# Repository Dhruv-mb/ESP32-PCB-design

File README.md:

ESP32-C3 Mini Evaluation Board

📌 Project Overview

This repository contains the KiCad hardware design files for a custom, compact ESP32-C3 (WROOM-02) mini evaluation board. Designed from scratch, this board functions as a standalone, breadboard-friendly tool tailored for rapid embedded development, IoT prototyping, and testing.

⚙️ Key Hardware Features

Microcontroller Core: Powered by the ESP32-C3-WROOM-02 module, offering Wi-Fi and Bluetooth LE capabilities in a highly compact footprint.

Robust Power Stage: Uses a USB-C receptacle for power input, equipped with ESD protection arrays and pi-filtering to ensure clean power. Voltage is stepped down using an AP2112 3.3V LDO regulator for stable delivery.

Native USB & Programming: The native USB differential pairs (D+ and D-) are routed directly to the microcontroller for seamless firmware flashing and debugging without needing an external UART bridge.

Precise RTC Clocking: Integrates a 32.768 kHz external crystal oscillator with precise load capacitors to support low-power Real-Time Clock (RTC) operations.

Boot & Reset Circuitry: Features hardware-debounced tactile switches with RC filters for manual Reset (EN pin) and Boot mode selection (IO9 strapping pin). Proper pull-up logic is implemented for SPI and Download boot modes.

Expansion & Prototyping: Peripheral GPIOs, 3.3V, and GND are broken out to standard 2.54mm pitch pin headers, perfectly spaced for breadboard integration.

🛠️ Tools Used

EDA Software: Designed using KiCad 9 (Schematic Capture and PCB Layout).

Firmware Target: Can be programmed via Arduino IDE or ESP-IDF using C/C++.

📂 Repository Structure

ESP32.kicad_sch: Schematic file detailing component connections and logical blocks.

ESP32.kicad_pcb: PCB layout file detailing trace routing, component placement, and differential pair routing.

ESP32.kicad_pro: KiCad project file.

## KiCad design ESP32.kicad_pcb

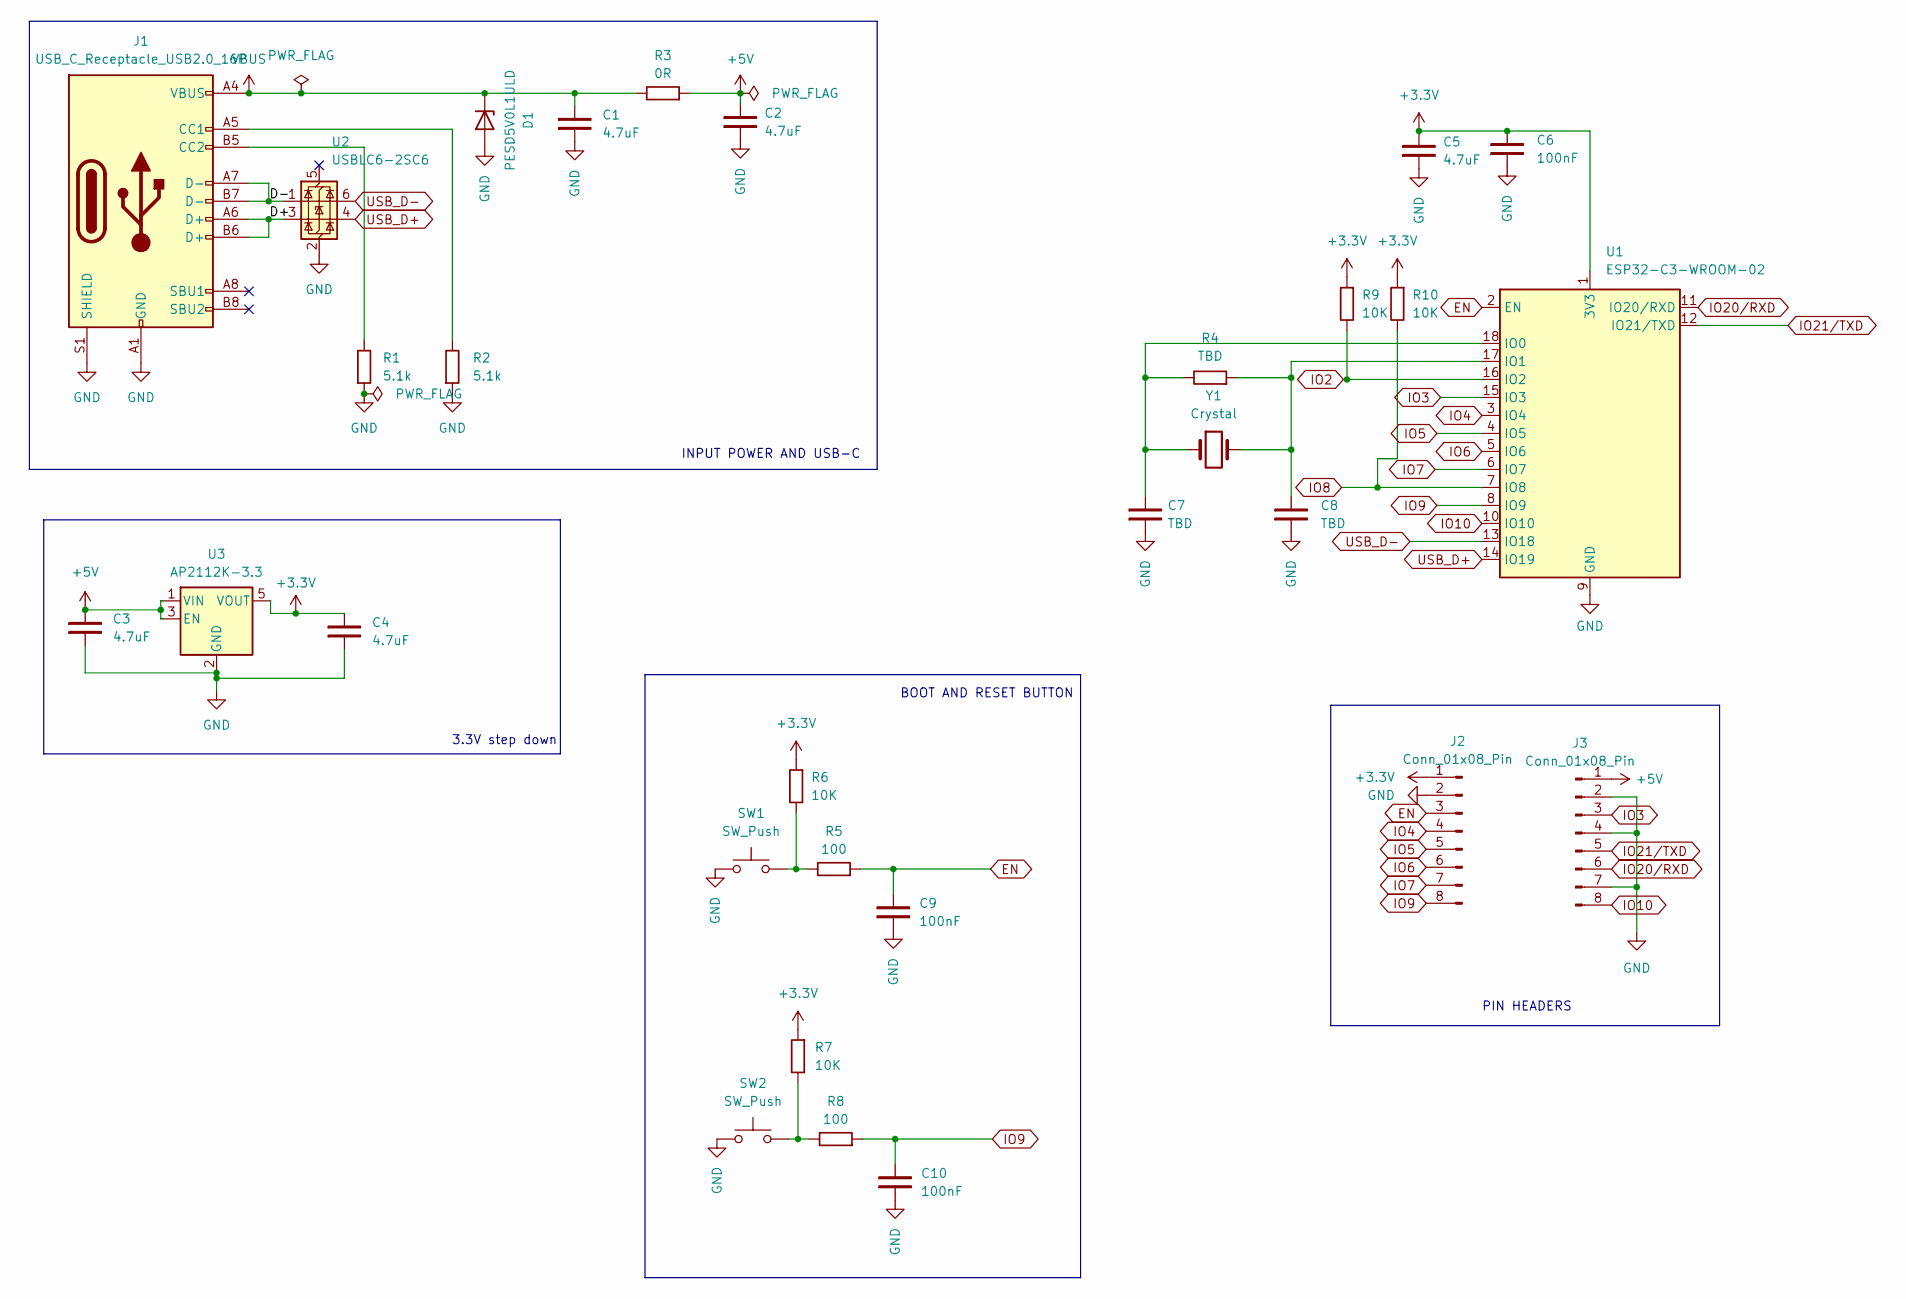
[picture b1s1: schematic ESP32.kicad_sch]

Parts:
C1, C2, C3, C4, C5: 4.7uF; CP_EIA-1608-08_AVX-J_HandSolder
C6, C9, C10: 100nF; CP_EIA-1608-08_AVX-J_HandSolder
C7, C8: TBD; CP_EIA-1608-08_AVX-J_HandSolder
D1: PESD5V0L1ULD; D_SOD-882D
J1: USB_C_Receptacle_USB2.0_16P; USB_C_Receptacle_GCT_USB4105-xx-A_16P_TopMnt_Horizontal
J2, J3: Conn_01x08_Pin; PinHeader_1x08_P2.54mm_Vertical
R1, R2: 5.1k; R_0201_0603Metric
R3: 0R; R_0201_0603Metric
R4: TBD; R_0201_0603Metric
R5, R8: 100; R_0201_0603Metric
R6, R7, R9, R10: 10K; R_0201_0603Metric
SW1, SW2: SW_Push; SW_SPST_B3U-1000P
U1: ESP32-C3-WROOM-02
U2: USBLC6-2SC6; SOT-23-6
U3: AP2112K-3.3; SOT-23-5
Y1: Crystal; Crystal_SMD_3215-2Pin_3.2x1.5mm

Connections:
+3.3V: C4.2, C5.2, C6.2, J2.1, R6.1, R7.1, R9.1, R10.1, U1.1 (3V3), U3.5 (VOUT)
+5V: C2.2, C3.2, J3.1, R3.1, U3.1 (VIN), U3.3 (EN)
/D+: J1.A6 (D+), J1.B6 (D+), U2.3 (I/O2)
/D-: J1.A7 (D-), J1.B7 (D-), U2.1 (I/O1)
EN: C9.2, J2.3, R5.1, U1.2 (EN)
GND: C1.1, C2.1, C3.1, C4.1, C5.1, C6.1, C7.1, C8.1, C9.1, C10.1, D1.2 (A), J1.A1 (GND), J1.A12 (GND), J1.B1 (GND), J1.B12 (GND), J1.S1 (SHIELD), J2.2, J3.2, J3.4, J3.7, R1.1, R2.1, SW1.1, SW2.1, U1.9 (GND), U1.19 (GND), U2.2 (GND), U3.2 (GND)
IO2: R9.2, U1.16 (IO2)
IO3: J3.3, U1.15 (IO3)
IO4: J2.4, U1.3 (IO4)
IO5: J2.5, U1.4 (IO5)
IO6: J2.6, U1.5 (IO6)
IO7: J2.7, U1.6 (IO7)
IO8: R10.2, U1.7 (IO8)
IO9: C10.2, J2.8, R8.1, U1.8 (IO9)
IO10: J3.8, U1.10 (IO10)
IO20/RXD: J3.6, U1.11 (IO20/RXD)
IO21/TXD: J3.5, U1.12 (IO21/TXD)
unnamed: J1.A5 (CC1), R2.2
unnamed: J1.B5 (CC2), R1.2
unnamed: R5.2, R6.2, SW1.2
unnamed: R7.2, R8.2, SW2.2
unnamed: C7.2, R4.2, U1.18 (IO0), Y1.1
unnamed: C8.2, R4.1, U1.17 (IO1), Y1.2
USB_D+: U1.14 (IO19), U2.4 (I/O2)
USB_D-: U1.13 (IO18), U2.6 (I/O1)
VBUS: C1.2, D1.1 (K), J1.A4 (VBUS), J1.A9 (VBUS), J1.B4 (VBUS), J1.B9 (VBUS), R3.2

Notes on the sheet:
BOOT AND RESET BUTTON
3.3V step down
INPUT POWER AND USB-C
PIN HEADERS

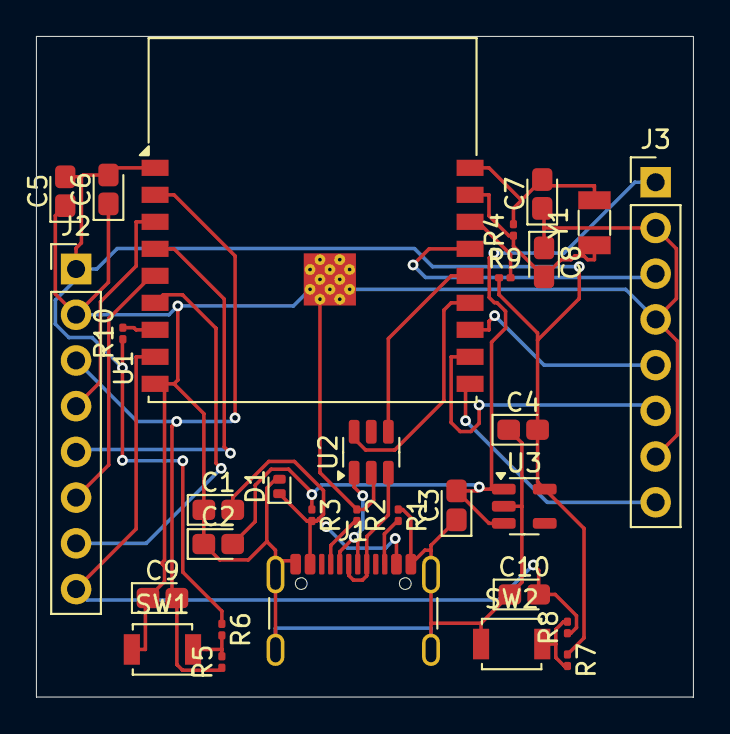
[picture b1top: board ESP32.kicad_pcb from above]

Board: 2 copper layers, 36.5 x 36.7 mm, 30 parts (0 on the bottom side), 26 nets.
